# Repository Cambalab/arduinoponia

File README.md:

# Arduinoponia
## Hacklab Camba

### **Resumen**
El objetivo del taller es utilizar un Arduino UNO para medir la luz ambiente y la humedad en el sustrato de una planta, mostrar la información mediante una interfaz de usuario y automatizar un sistema de riego por goteo si la humedad cae por debajo de un umbral.

### **Elementos necesarios**
Se tratara de utilizar elementos reciclados siempre que sea posible y se tratara de abaratar costos y enfocarse no en la exactitud del dispositivo, sino mas bien el uso de herramientas comunes que nos permitan conocer mas sobre los componentes y su funcionamiento. Como por ejemplo, al utilizar los clavos para medir la humedad de la tierra, estamos creando una resistencia variable, basada en la conductividad de la tierra, la cual es mayor cuando esta humeda, y menor cuando esta seca.

**Medidor de Humedad del sustrato: **
- Clavos, preferentemente galvanizados, para evitar que se oxiden.

**Sistema de riego por goteo:**
- Botella de agua o un tetrabrick a modo de tanque de agua.
- Mangueras de plastica de 6mm de diametro externo y 4mm interno.
- Conecciones de 3 vias (tambien de acuario gg)
- Pistola de calor para sellar la union de la manguera con el tanque.

**Interfaz de usuario:**

- **3 leds Amarillos** representan la lista de los *sensores disponibles*. El led apagado indica que el sensor esta desconectado. El led encendido indica que el sensor esta conectado y el led titilante indica que el sensor esta *seleccionado*.
- **3 leds Verdes** representan el *valor actual* que esta midiendo el *sensor seleccionado* en una medida de 0 a 100%.
- **1 leds azules** representa el *Actuador*, de igual manera que los sensores, titilara para indicar que ese *esta Activo*.
- **1 boton** nos permitira *seleccionar* los diferentes sensores.
- **1 shift-registers (74HC595)** nos permitira utilizar unos pocos pines del arduino para controlar todos los leds.
- **7 resistencias de 470ohm** para protejer los leds.
- **1 resistencias de 1Kohm** para protejer los leds.

### **Links utiles**
https://www.arduino.cc/en/Tutorial/ShiftIn
https://www.arduino.cc/en/Tutorial/ShiftOut
https://www.arduino.cc/reference/en/language/functions/math/constrain/
https://www.arduino.cc/reference/en/language/functions/math/map/
https://www.arduino.cc/reference/en/language/functions/analog-io/analogread/

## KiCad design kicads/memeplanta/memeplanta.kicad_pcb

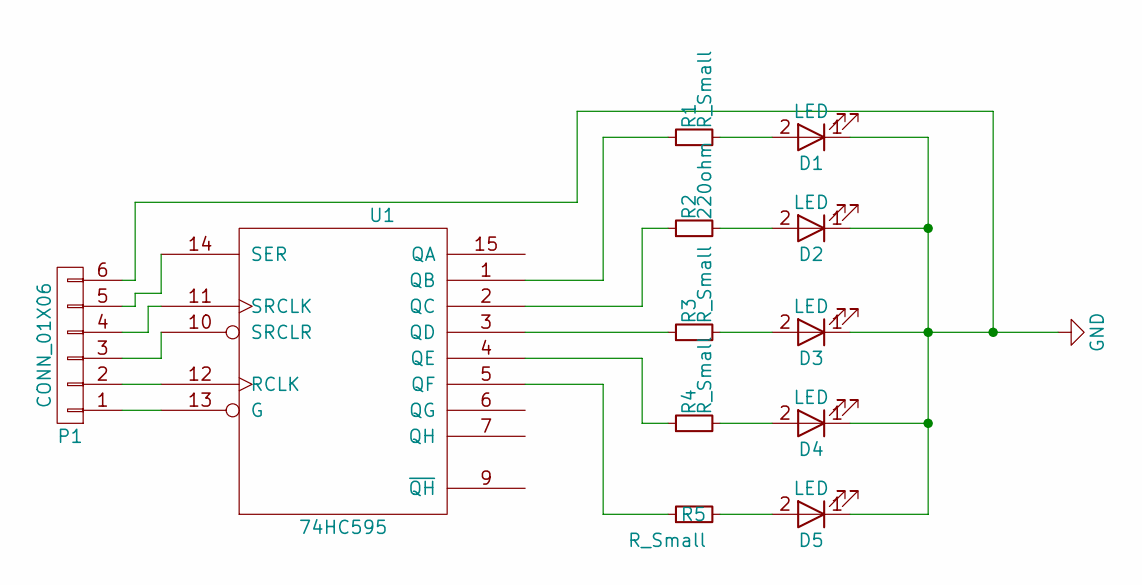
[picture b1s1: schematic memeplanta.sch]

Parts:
D1, D2, D3, D4, D5: LED; LED-5MM
P1: CONN_01X06; Pin_Header_Straight_1x06
R1, R3, R4, R5: R_Small; R_0805_HandSoldering
R2: 220ohm; R_0805_HandSoldering
U1: 74HC595; SO-16-N

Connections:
GND: D1.1 (K), D2.1 (K), D3.1 (K), D4.1 (K), D5.1 (K), P1.6, U1.8 (GND)
unnamed: D1.2 (A), R1.2
unnamed: D2.2 (A), R2.2
unnamed: D3.2 (A), R3.2
unnamed: D4.2 (A), R4.2
unnamed: D5.2 (A), R5.2
unnamed: R1.1, U1.1 (QB)
unnamed: R2.1, U1.2 (QC)
unnamed: R3.1, U1.3 (QD)
unnamed: R4.1, U1.4 (QE)
unnamed: R5.1, U1.5 (QF)
unnamed: P1.3, U1.10 (SRCLR)
unnamed: P1.4, U1.11 (SRCLK)
unnamed: P1.2, U1.12 (RCLK)
unnamed: P1.1, U1.13 (G)
unnamed: P1.5, U1.14 (SER)
VCC: U1.16 (VCC)

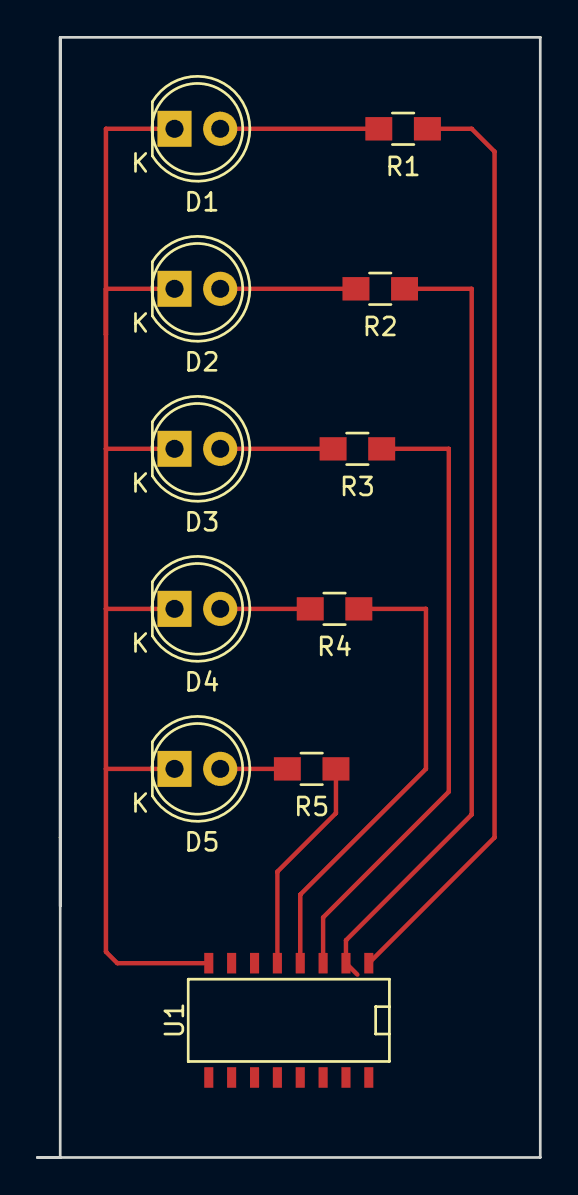
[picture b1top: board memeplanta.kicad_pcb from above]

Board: 2 copper layers, 27.9 x 62.2 mm, 11 parts (0 on the bottom side), 11 nets.

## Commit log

2018-11-10 arduinoponia para actividad hacklab
